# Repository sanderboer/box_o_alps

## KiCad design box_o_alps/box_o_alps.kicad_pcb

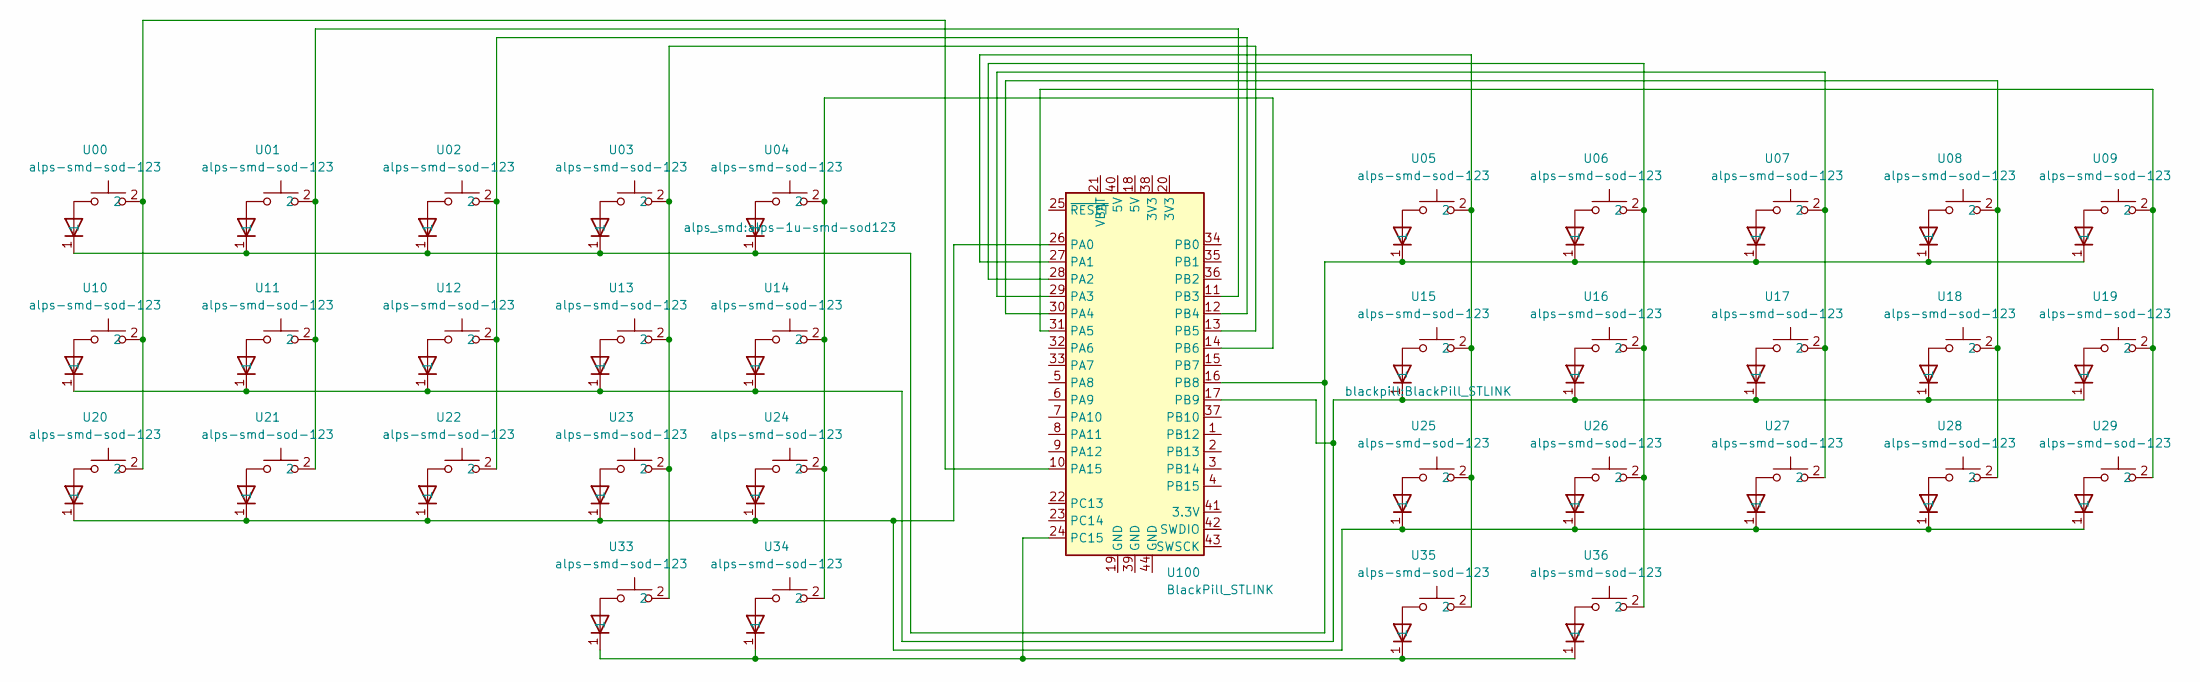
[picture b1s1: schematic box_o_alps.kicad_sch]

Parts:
U00, U01, U02, U03, U04, U05, U06, U07, U08, U09, U10, U11, U12, U13, U14, U15, U16, U17, U18, U19, U20, U21, U22, U23, U24, U25, U26, U27, U28, U29, U33, U34, U35, U36: alps-smd-sod-123; alps-1u-smd-sod123
U100: BlackPill_STLINK

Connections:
unnamed: U00.1, U01.1, U02.1, U03.1, U04.1, U05.1, U06.1, U07.1, U08.1, U09.1, U100.16 (PB8)
unnamed: U00.2, U10.2, U20.2, U100.10 (PA15)
unnamed: U01.2, U11.2, U21.2, U100.11 (PB3)
unnamed: U02.2, U12.2, U22.2, U100.12 (PB4)
unnamed: U03.2, U13.2, U23.2, U33.2, U100.13 (PB5)
unnamed: U04.2, U14.2, U24.2, U34.2, U100.14 (PB6)
unnamed: U05.2, U15.2, U25.2, U35.2, U100.27 (PA1)
unnamed: U06.2, U16.2, U26.2, U36.2, U100.28 (PA2)
unnamed: U07.2, U17.2, U27.2, U100.29 (PA3)
unnamed: U08.2, U18.2, U28.2, U100.30 (PA4)
unnamed: U09.2, U19.2, U29.2, U100.31 (PA5)
unnamed: U10.1, U11.1, U12.1, U13.1, U14.1, U15.1, U16.1, U17.1, U18.1, U19.1, U100.17 (PB9)
unnamed: U20.1, U21.1, U22.1, U23.1, U24.1, U25.1, U26.1, U27.1, U28.1, U29.1, U100.26 (PA0)
unnamed: U33.1, U34.1, U35.1, U36.1, U100.24 (PC15)

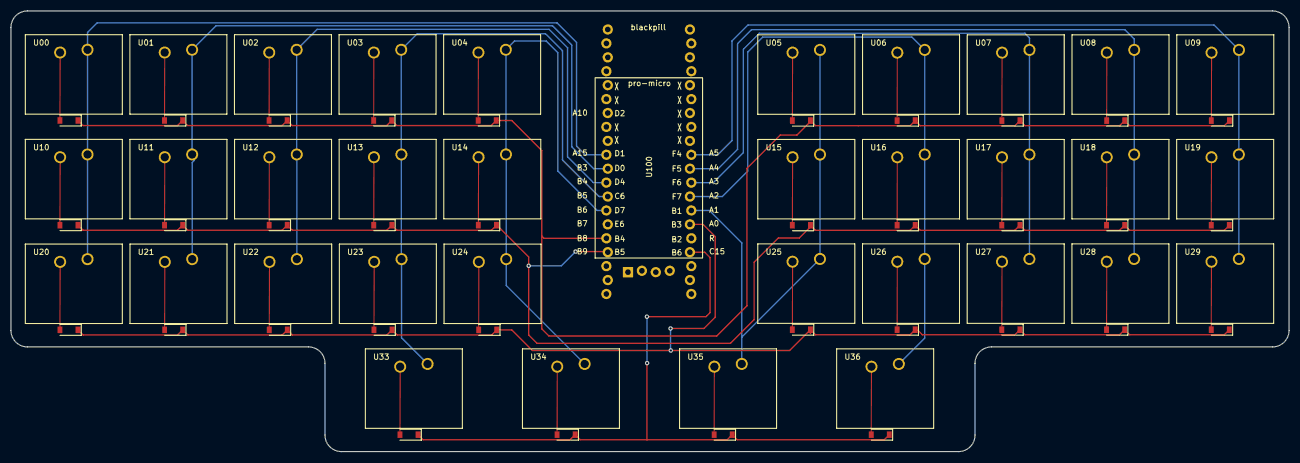
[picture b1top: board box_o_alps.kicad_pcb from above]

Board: 2 copper layers, 233.2 x 80.4 mm, 35 parts (0 on the bottom side), 14 nets.

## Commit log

2022-09-03 Too lazy to comment
2022-10-06 some gridfinity cubes remade the blender way
2023-02-14 yask
2023-09-25 ... intermediate commit
